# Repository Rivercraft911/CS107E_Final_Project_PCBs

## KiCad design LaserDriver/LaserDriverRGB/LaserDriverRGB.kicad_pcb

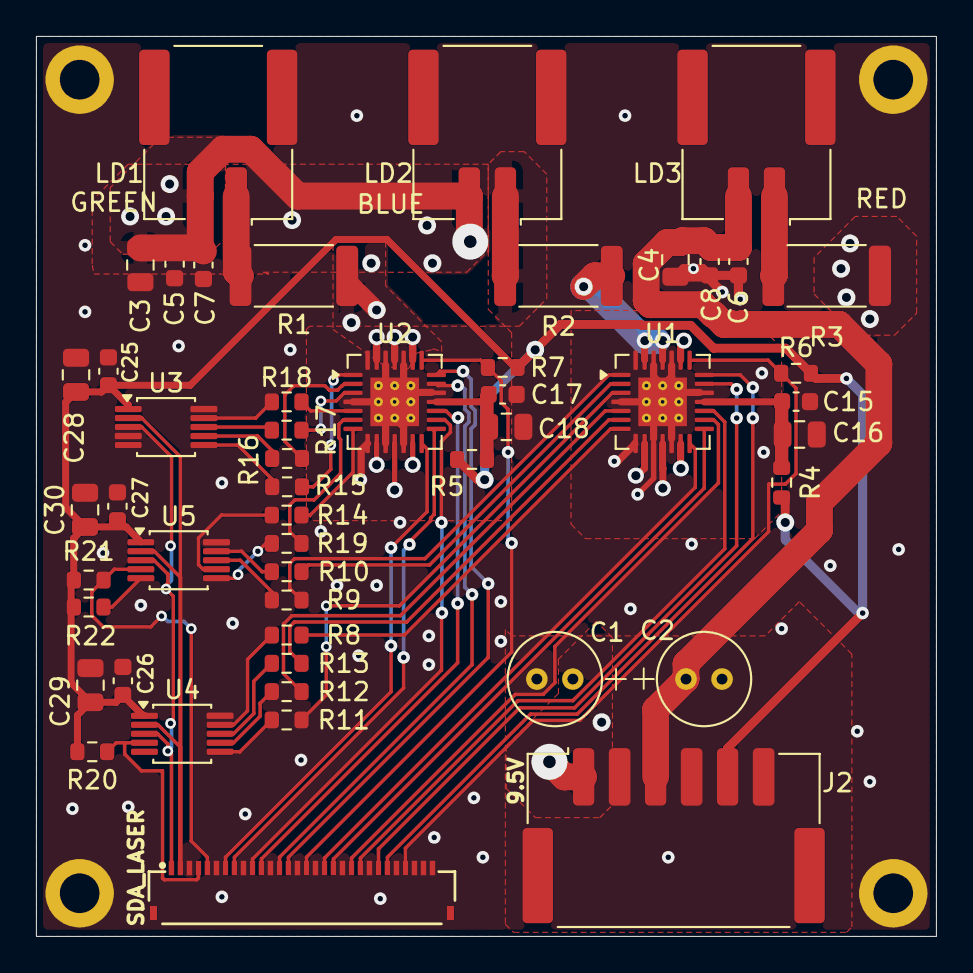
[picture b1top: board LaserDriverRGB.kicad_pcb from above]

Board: 4 copper layers, 50.0 x 50.0 mm, 55 parts (1 on the bottom side), 55 nets.

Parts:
C1, C2: 100uF; C_Radial_D5.0mm_H5.0mm_P2.00mm
C3, C4, C16, C18, C28, C29, C30: 10uF; C_0805_2012Metric
C5, C6, C15, C17, C25, C26, C27: 0.1uF; C_0603_1608Metric
C7, C8: 10nF; C_0603_1608Metric
H1, H2, H3, H4: MountingHole_Pad; MountingHole_2.2mm_M2_DIN965_Pad
HS1: Heatsink_Pad; TestPoint_Pad_4.0x4.0mm
J1: SIGNAL; FPC_1x30_P0.5mm_Horizontal_DualContact
J2: POWER; Molex_DuraClik_502352-0600_1x06-1MP_P2.00mm_Horizontal
LD1: GREEN; Molex_DuraClik_502352-0200_1x02-1MP_P2.00mm_Horizontal
LD2: BLUE; Molex_DuraClik_502352-0200_1x02-1MP_P2.00mm_Horizontal
LD3: RED; Molex_DuraClik_502352-0200_1x02-1MP_P2.00mm_Horizontal
R1, R2, R3: 0.1; R_2512_6332Metric
R4, R5: 1; R_0603_1608Metric
R6, R7: 10K; R_0603_1608Metric
R8, R9, R10, R11, R12, R13, R14, R15, R16, R17, R18, R19: 1k; R_0603_1608Metric
R20, R21, R22: 100k; R_0603_1608Metric
U1, U2: QFN-28-1EP_5x5mm_P0.5mm_EP2.7x2.7mm_ThermalVias
U3, U4, U5: MCP4728; MSOP-10_3x3mm_P0.5mm

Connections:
3V3: C25.1, C26.1, C27.1, C28.1, C29.1, C30.1, J2.5, R4.1, R5.2, R6.2, R7.2, R20.2, R21.2, R22.1, U3.1 (VDD), U4.1 (VDD), U5.1 (VDD)
+5.5V: C2.1, C4.1, C6.1, C8.1, J2.3, LD3.2 (A)
+9.5V: C1.1, C3.1, C5.1, C7.1, J2.1, LD1.2 (A), LD2.2 (A)
BLUE_CATH: R2.2, U1.25 (LDK2), U1.27 (LDK1), U2.9 (LDK6), U2.11 (LDK5)
BLUE_EN1: J1.8, U2.15 (EN5)
BLUE_EN2: J1.7, U2.14 (EN6)
BLUE_EN3: J1.25, U1.21 (EN1)
BLUE_EN4: J1.24, U1.20 (EN2)
C_SET_BLUE_1: R19.2, U5.6 (VOUTA)
C_SET_BLUE_2: R14.2, U5.7 (VOUTB)
C_SET_BLUE_3: R9.2, U5.8 (VOUTC)
C_SET_BLUE_4: R10.2, U5.9 (VOUTD)
C_SET_GREEN_1: R15.2, U3.6 (VOUTA)
C_SET_GREEN_2: R16.2, U3.7 (VOUTB)
C_SET_GREEN_3: R17.2, U3.8 (VOUTC)
C_SET_GREEN_4: R18.2, U3.9 (VOUTD)
C_SET_RED_1: R11.2, U4.6 (VOUTA)
C_SET_RED_2: R12.2, U4.7 (VOUTB)
C_SET_RED_3: R13.2, U4.8 (VOUTC)
C_SET_RED_4: R8.2, U4.9 (VOUTD)
GND: C1.2, C2.2, C3.2, C4.2, C5.2, C6.2, C7.2, C8.2, C15.2, C16.2, C17.2, C18.2, C25.2, C26.2, C27.2, C28.2, C29.2, C30.2, H1.1 (1_1), H2.1 (1_1), H3.1 (1_1), H4.1 (1_1), HS1.1, J1.3, J1.6, J1.9, J1.12, J1.15, J1.17, J1.20, J1.23, J1.26, J1.28, J1.29, J1.30, J2.2, J2.4, J2.6, U1.4 (GND), U1.8 (AGND6), U1.10 (AGND5), U1.12 (AGND4), U1.19 (ELVDS), U1.24 (AGND3), U1.26 (AGND2), U1.28 (AGND1), U1.29 (EPAD), U2.4 (GND), U2.8 (AGND6), U2.10 (AGND5), U2.12 (AGND4), U2.19 (ELVDS), U2.24 (AGND3), U2.26 (AGND2), U2.28 (AGND1), U2.29 (EPAD), U3.4 (~LDAC), U3.10 (VSS), U4.10 (VSS), U5.10 (VSS)
GREEN_CATH: R1.2, U2.13 (LDK4), U2.23 (LDK3), U2.25 (LDK2), U2.27 (LDK1)
GR_EN1: J1.14, U2.21 (EN1)
GR_EN2: J1.13, U2.20 (EN2)
GR_EN3: J1.11, U2.17 (EN3)
GR_EN4: J1.10, U2.16 (EN4)
LDAC1: J1.4, R20.1, U4.4 (~LDAC)
LDAC2: J1.5, R21.1, U5.4 (~LDAC)
unnamed: LD1.1 (K), R1.1
unnamed: LD2.1 (K), R2.1
unnamed: LD3.1 (K), R3.1
unnamed: R9.1, U1.1 (CI1)
unnamed: R10.1, U1.2 (CI2)
unnamed: R11.1, U1.3 (CI3)
unnamed: R12.1, U1.5 (CI4)
unnamed: R13.1, U1.6 (CI5)
unnamed: R8.1, U1.7 (CI6)
unnamed: C15.1, C16.1, R4.2, U1.18 (VDD)
unnamed: R15.1, U2.1 (CI1)
unnamed: R16.1, U2.2 (CI2)
unnamed: R17.1, U2.3 (CI3)
unnamed: R18.1, U2.5 (CI4)
unnamed: R19.1, U2.6 (CI5)
unnamed: R14.1, U2.7 (CI6)
unnamed: C17.1, C18.1, R5.1, U2.18 (VDD)
unnamed: R22.2, U5.5 (RDY/~BSY)
RED_CATH: R3.2, U1.9 (LDK6), U1.11 (LDK5), U1.13 (LDK4), U1.23 (LDK3)
RED_EN1: J1.22, U1.17 (EN3)
RED_EN2: J1.21, U1.16 (EN4)
RED_EN3: J1.19, U1.15 (EN5)
RED_EN4: J1.18, U1.14 (EN6)
SCL_LASER: J1.2, U3.2 (SCL), U4.2 (SCL), U5.2 (SCL)
SDA_LASER: J1.1, U3.3 (SDA), U4.3 (SDA), U5.3 (SDA)
SW_ER_1: J1.16, R7.1, U2.22 (NER)
SW_ER_2: J1.27, R6.1, U1.22 (NER)

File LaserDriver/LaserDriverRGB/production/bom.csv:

Designator,Footprint,Quantity,Value,LCSC Part #
"C1, C2",C_Radial_D5.0mm_H5.0mm_P2.00mm,2,100uF,
"C15, C17, C25, C26, C27, C5, C6",0603,7,0.1uF,
"C16, C18, C28, C29, C3, C30, C4",0805,7,10uF,
"C7, C8",0603,2,10nF,
HS1,TestPoint_Pad_4.0x4.0mm,1,Heatsink_Pad,
J1,FPC_1x30_P0.5mm_Horizontal_DualContact,1,SIGNAL,
J2,Molex_DuraClik_502352-0600_1x06-1MP_P2.00mm_Horizontal,1,POWER,
LD1,Molex_DuraClik_502352-0200_1x02-1MP_P2.00mm_Horizontal,1,GREEN,
LD2,Molex_DuraClik_502352-0200_1x02-1MP_P2.00mm_Horizontal,1,BLUE,
LD3,Molex_DuraClik_502352-0200_1x02-1MP_P2.00mm_Horizontal,1,RED,
"R1, R2, R3",2512,3,0.1,
"R10, R11, R12, R13, R14, R15, R16, R17, R18, R19, R8, R9",0603,12,1k,
"R20, R21, R22",0603,3,100k,
"R4, R5",0603,2,1,
"R6, R7",0603,2,10K,
"U1, U2",QFN-28-1EP_5x5mm_P0.5mm_EP2.7x2.7mm_ThermalVias,2,~,
"U3, U4, U5",MSOP-10_3x3mm_P0.5mm,3,MCP4728,

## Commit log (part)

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2026-05-26 yeah yeah?
2026-05-26 pcb chilling
2026-05-26 fixed
2026-05-27 rounded fillets
